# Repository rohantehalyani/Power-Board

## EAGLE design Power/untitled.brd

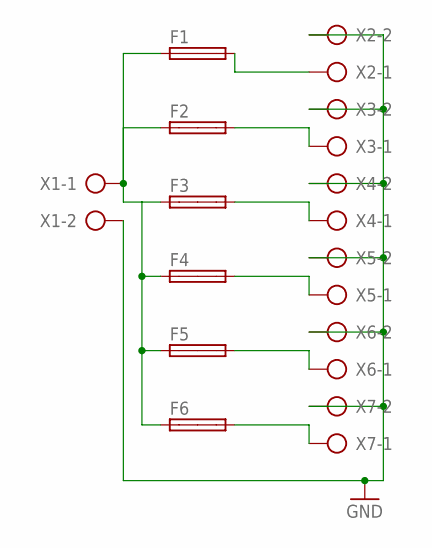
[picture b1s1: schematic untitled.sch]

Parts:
F1, F2, F3, F4, F5, F6: SHK20Q
X1, X2, X3, X4, X5, X6, X7: AK500/2-H

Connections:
GND: X1.2, X2.2, X3.2, X4.2, X5.2, X6.2, X7.2
unnamed: F1.1A, F2.1A, F3.1A, F4.1A, F5.1A, F6.1A, X1.1
unnamed: F1.2A, X2.1
unnamed: F2.2A, X3.1
unnamed: F3.2A, X4.1
unnamed: F4.2A, X5.1
unnamed: F5.2A, X6.1
unnamed: F6.2A, X7.1

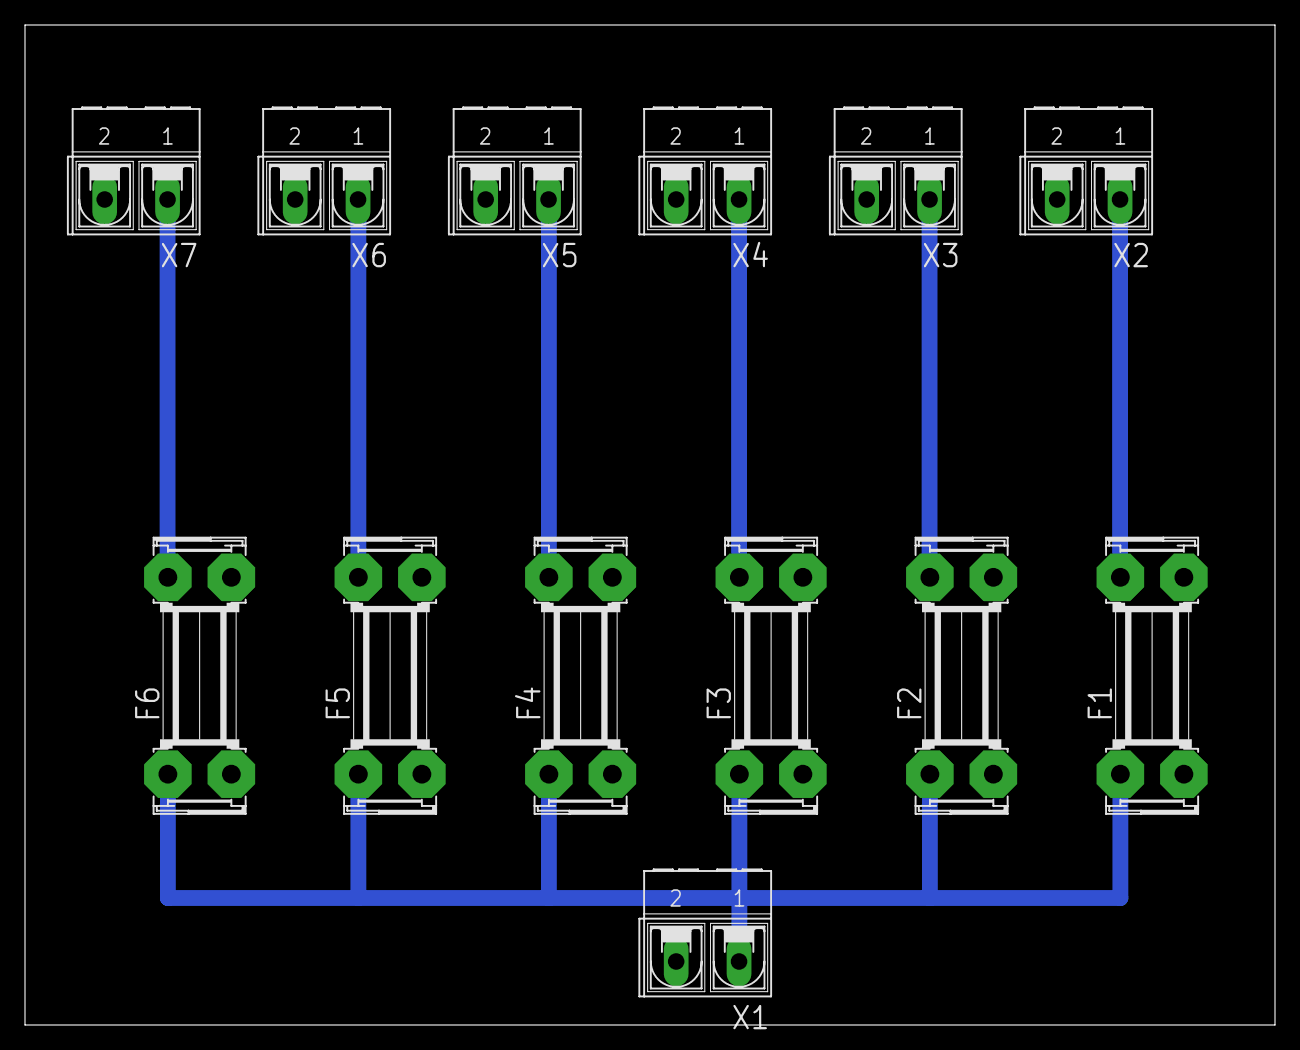
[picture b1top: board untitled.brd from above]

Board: 2 copper layers, 100.0 x 80.0 mm, 13 parts (0 on the bottom side), 8 nets.

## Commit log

2020-02-11 Eagle Board for ROV Power
